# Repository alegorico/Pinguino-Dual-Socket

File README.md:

# Pinguino 8bit Dual Socket (Pinguino mm8)

Eagle para la creacion de una placa `Like Pinguino`

Esta pensado para usar tanto el micro (pic) 18f2550 como el 18f4550 (pero no al mismo tiempo)

para mas informacion visite la wiki de [pinguino.cc](http://www.pinguino.cc/wiki/index.php?title=Pinguino_mm8_dual/es)

o visite el instructable
[http://www.instructables.com/id/Pinguino-Mm8/](http://www.instructables.com/id/Pinguino-Mm8/)

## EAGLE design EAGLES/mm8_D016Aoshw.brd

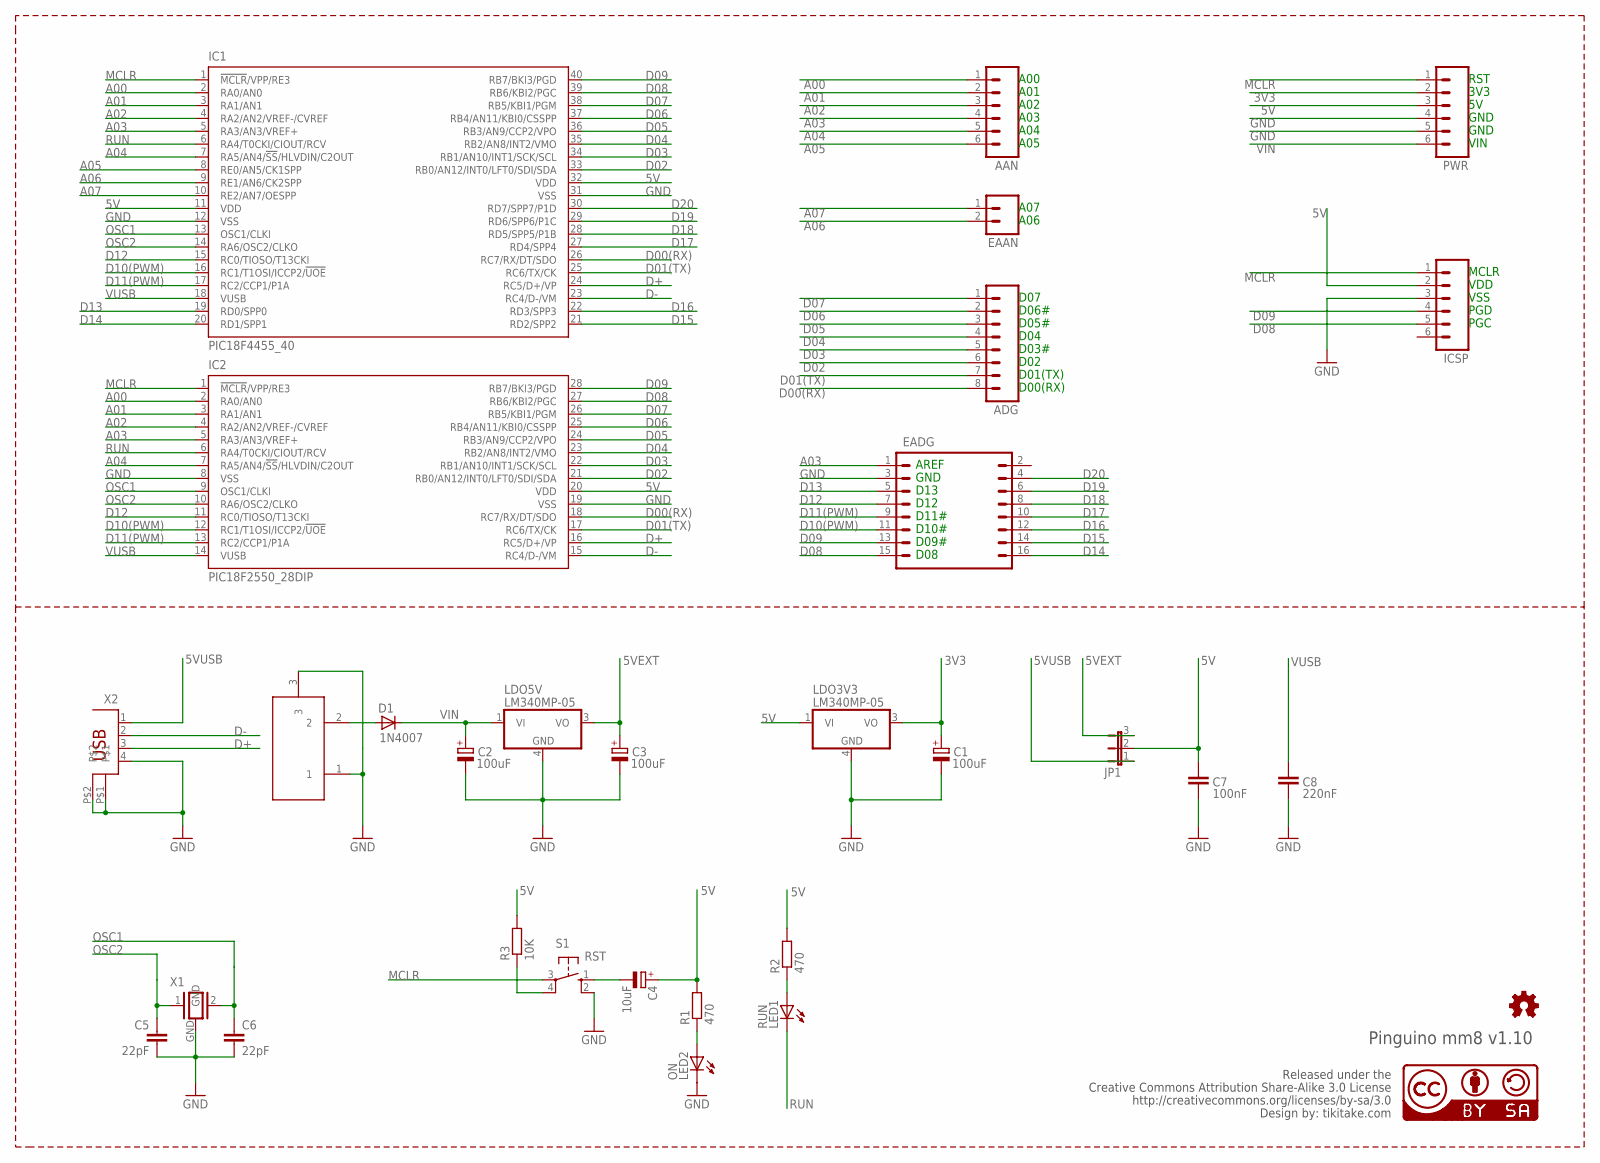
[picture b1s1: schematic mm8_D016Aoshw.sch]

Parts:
AAN: M06SIP; 1X06
ADG: M08; 1X08
C1, C2, C3: 100uF; E2-5
C4: 10uF; E2-5
C5, C6: 22pF; C5B2.5N
C7: 100nF; C5B2.5N
C8: 220nF; C5B2.5N
D1: 1N4007; DO41-7
EAAN: M02PTH; 1X02
EADG: M08X2; 2X8
IC1: PIC18F4455_40; DIL40
IC2: PIC18F2550_28DIP; DIL28-3
ICSP: M06SIP; 1X06
JP1: JP2E; JP2
LDO3V3, LDO5V: LM340MP-05; SOT223
LED1: RUN; LED3MM
LED2: ON; LED3MM
LOGO1: OSHW_LOGO_FILLX0150-NT; OSHW_FILLX150_NOTEXT
PWR: M06SIP; 1X06
R1, R2: 470; 0207/7
R3: 10K; 0207/7
S1: RST; B3F-10XX
U$3: CC-BY-SA
X1: RESONATOR; QS3
X2: PN61729
X4: DC21MMX; DC-21MM

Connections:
3V3: C1.+, LDO3V3.3 (VO), PWR.2
5V: C4.+, C7.1, IC1.11 (VDD), IC1.32 (VDD), IC2.20 (VDD), ICSP.2, JP1.2, LDO3V3.1 (VI), PWR.3, R1.2, R2.2, R3.2
5VEXT: C3.+, JP1.3, LDO5V.3 (VO)
5VUSB: JP1.1, X2.1
A00: AAN.1, IC1.2 (RA0/AN0), IC2.2 (RA0/AN0)
A01: AAN.2, IC1.3 (RA1/AN1), IC2.3 (RA1/AN1)
A02: AAN.3, IC1.4 (RA2/AN2/VREF-/CVREF), IC2.4 (RA2/AN2/VREF-/CVREF)
A03: AAN.4, EADG.1, IC1.5 (RA3/AN3/VREF+), IC2.5 (RA3/AN3/VREF+)
A04: AAN.5, IC1.7 (RA5/AN4/!SS!/HLVDIN/C2OUT), IC2.7 (RA5/AN4/!SS!/HLVDIN/C2OUT)
A05: AAN.6, IC1.8 (RE0/AN5/CK1SPP)
A06: EAAN.2, IC1.9 (RE1/AN6/CK2SPP)
A07: EAAN.1, IC1.10 (RE2/AN7/OESPP)
D00(RX): ADG.8, IC1.26 (RC7/RX/DT/SDO), IC2.18 (RC7/RX/DT/SDO)
D01(TX): ADG.7, IC1.25 (RC6/TX/CK), IC2.17 (RC6/TX/CK)
D02: ADG.6, IC1.33 (RB0/AN12/INT0/LFT0/SDI/SDA), IC2.21 (RB0/AN12/INT0/LFT0/SDI/SDA)
D03: ADG.5, IC1.34 (RB1/AN10/INT1/SCK/SCL), IC2.22 (RB1/AN10/INT1/SCK/SCL)
D04: ADG.4, IC1.35 (RB2/AN8/INT2/VMO), IC2.23 (RB2/AN8/INT2/VMO)
D05: ADG.3, IC1.36 (RB3/AN9/CCP2/VPO), IC2.24 (RB3/AN9/CCP2/VPO)
D06: ADG.2, IC1.37 (RB4/AN11/KBI0/CSSPP), IC2.25 (RB4/AN11/KBI0/CSSPP)
D07: ADG.1, IC1.38 (RB5/KBI1/PGM), IC2.26 (RB5/KBI1/PGM)
D08: EADG.15, IC1.39 (RB6/KBI2/PGC), IC2.27 (RB6/KBI2/PGC), ICSP.5
D09: EADG.13, IC1.40 (RB7/BKI3/PGD), IC2.28 (RB7/BKI3/PGD), ICSP.4
D10(PWM): EADG.11, IC1.16 (RC1/T1OSI/ICCP2/!UOE), IC2.12 (RC1/T1OSI/ICCP2/!UOE)
D11(PWM): EADG.9, IC1.17 (RC2/CCP1/P1A), IC2.13 (RC2/CCP1/P1A)
D12: EADG.7, IC1.15 (RC0/TIOSO/T13CKI), IC2.11 (RC0/TIOSO/T13CKI)
D13: EADG.5, IC1.19 (RD0/SPP0)
D14: EADG.16, IC1.20 (RD1/SPP1)
D15: EADG.14, IC1.21 (RD2/SPP2)
D16: EADG.12, IC1.22 (RD3/SPP3)
D17: EADG.10, IC1.27 (RD4/SPP4)
D18: EADG.8, IC1.28 (RD5/SPP5/P1B)
D19: EADG.6, IC1.29 (RD6/SPP6/P1C)
D20: EADG.4, IC1.30 (RD7/SPP7/P1D)
D+: IC1.24 (RC5/D+/VP), IC2.16 (RC5/D+/VP), X2.3
D-: IC1.23 (RC4/D-/VM), IC2.15 (RC4/D-/VM), X2.2
GND: C1.-, C2.-, C3.-, C5.2, C6.2, C7.2, C8.2, EADG.3, IC1.12 (VSS), IC1.31 (VSS), IC2.8 (VSS), IC2.19 (VSS), ICSP.3, LDO3V3.4 (GND), LDO5V.4 (GND), LED2.K (C), PWR.4, PWR.5, S1.2 (S1), X1.GND, X2.4, X2.P$1, X2.P$2, X4.1, X4.3
MCLR: IC1.1 (!MCLR!/VPP/RE3), IC2.1 (!MCLR!/VPP/RE3), ICSP.1, PWR.1, S1.3
unnamed: LED2.A, R1.1
unnamed: R3.1, S1.4 (P1)
unnamed: D1.A, X4.2
unnamed: LED1.A, R2.1
unnamed: C4.-, S1.1 (S)
OSC1: C6.1, IC1.13 (OSC1/CLKI), IC2.9 (OSC1/CLKI), X1.2
OSC2: C5.1, IC1.14 (RA6/OSC2/CLKO), IC2.10 (RA6/OSC2/CLKO), X1.1
RUN: IC1.6 (RA4/T0CKI/CIOUT/RCV), IC2.6 (RA4/T0CKI/CIOUT/RCV), LED1.K (C)
VIN: C2.+, D1.C, LDO5V.1 (VI), PWR.6
VUSB: C8.1, IC1.18 (VUSB), IC2.14 (VUSB)

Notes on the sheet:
D00(RX)
D01(TX)
D02
D03#
D04
D05#
D06#
D07
D08
D09#
D10#
D11#
D12
D13
GND
AREF
A00
A01
A02
A03
A04
A05
VIN
3V3
RST
A06
A07
PGC
PGD
VSS
VDD
MCLR
Creative Commons Attribution Share-Alike 3.0 License
http://creativecommons.org/licenses/by-sa/3.0
Design by: tikitake.com
Released under the
Pinguino mm8 v1.10

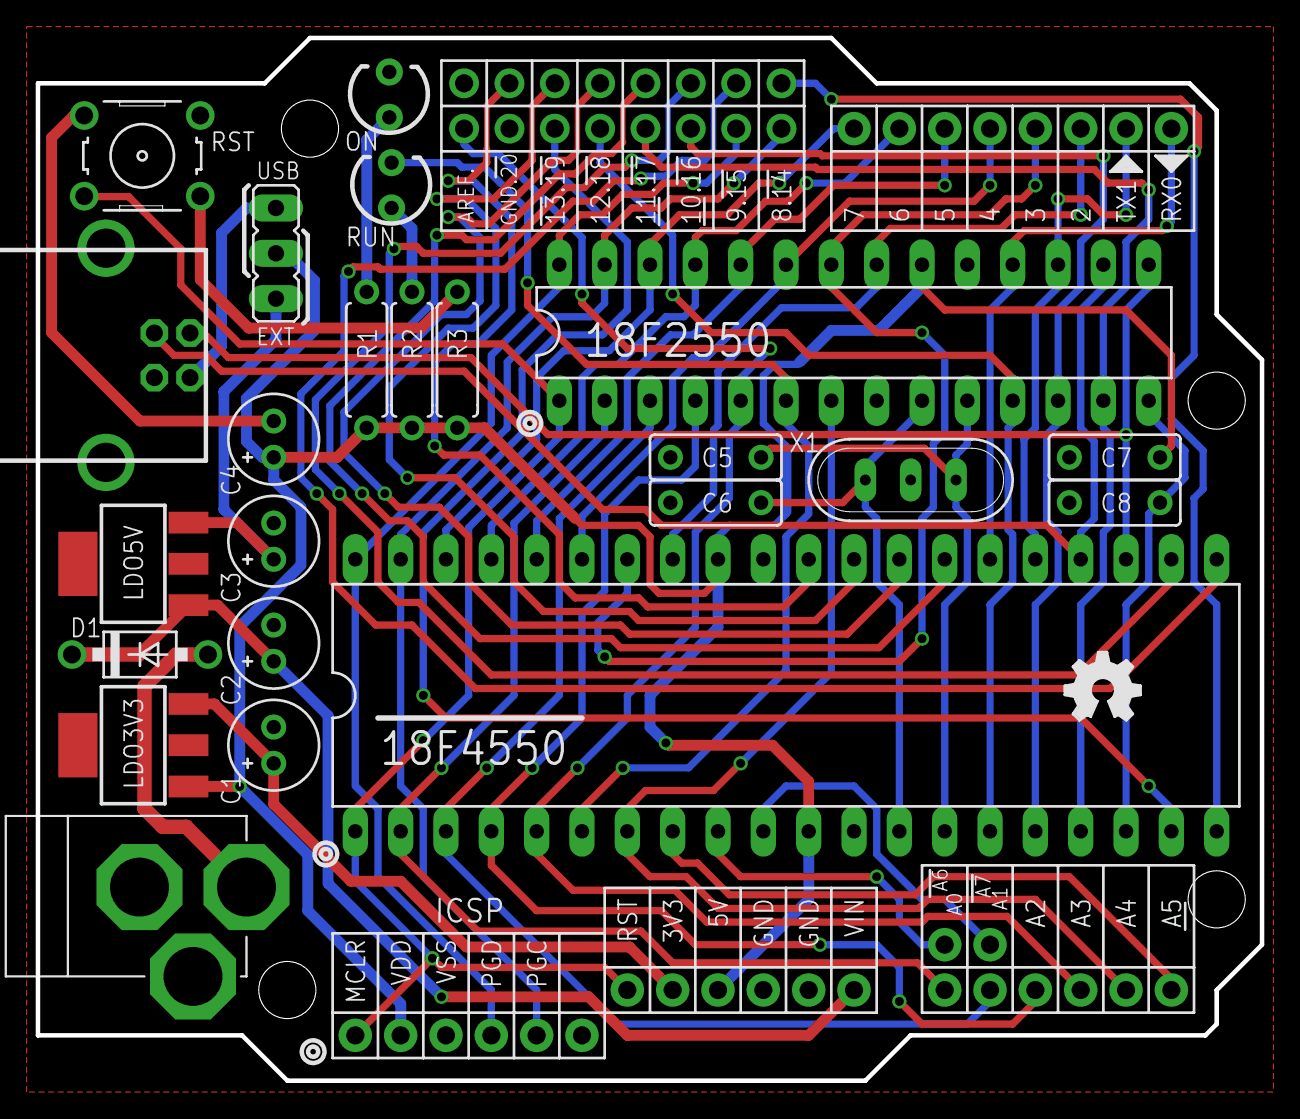
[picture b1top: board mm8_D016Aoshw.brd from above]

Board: 2 copper layers, 68.6 x 58.4 mm, 31 parts (0 on the bottom side), 47 nets.

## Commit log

2016-01-16 Init Doc
2016-01-16 EAGLE Doc ver 1.10.2
2016-01-16 add info instructable.com
2016-01-16 Gerbers files v.D016
2016-01-16 Gerbers files v.D016A
2016-01-16 edit readme
2016-01-16 add document
2016-01-16 inclucion de la referencia a la wiki

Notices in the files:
EAGLES/mm8_D016Aoshw.brd:
Released under the Creative Commons Attribution Share-Alike 3.0 License
